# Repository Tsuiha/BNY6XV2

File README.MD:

# BNY6X V2

「BNY6X V2」は2025年に製作した60%キーボードです。  
多親指キー＋矢印キー配列、MXとロープロに両対応、GH60互換ケース対応、の特徴があります。

---

## BNY6X V2 PCB

- **キー配列**
60%レイアウト  
親指キー、矢印キーを備えた最下行  

[Keyboard Layout Editor](https://www.keyboard-layout-editor.com/)

- **対応マウント方式**
GH60互換設計で、6か所のネジ穴が設けられています。  
加えて外周に5か所の切り欠きが設けられており、独自のプレートマウントにも対応します。

- **対応スイッチ**
「Cherry MX 」または「KS-33B GateronLowProfile 3.0」に互換性のあるスイッチが使用できます。  
キースイッチはMX用ホットスワップソケットにてPCBに接続します。
ロープロ対応及び低背化のため基板は1.2mm を使用します。

- **サイドスイッチ**
背面type-C横には3方向（左、右、押し込み）のレバースイッチが取り付け可能です。  
既製品のGH60互換ケースに使用する際は、干渉するためレバースイッチは実装しない必要があります。

- **対応スタビライザー**
プレートマウントのスタビライザーにのみ対応します。  
またMXスイッチの場合スタビライザー下が開いているため、ケース取り付け前に予めスタビライザー部のキーキャップは取り付けておく必要があります。

- **Firmware**
QMK Fimware, [BNY6X V2 codes](https://github.com/Tsuiha/vial-qmk/tree/vial/keyboards/0_tsuiha/bny6x_v2)

---

## BNY6X V2 typeT

1ピースでCNC加工を想定したGH60互換トレイケースです。

- **マウント箇所**
左右4か所のみネジ受けを設けており、中央2か所は省いています。  
ねじ止めで位置を固定し、ボトムフォームで基板を保持する機構です。

- **フロントベゼル幅**
フロントトップのベゼルをカットし幅を抑えています。  
指付け根でのキー入力時に干渉しにくいです。

- **低背設計**
高さを抑えているため、手前部に背の高い実装部品や下付きソケットの基板の場合ケースに干渉する恐れがあります。

- **チルト角**
6度固定です。

- **type-C開口**
上方向に余裕があるため、手前部に基板の干渉がある場合、スタンドオフにスペーサを噛ませることで干渉を回避できます。  
また横方向のtype-C位置はGH60、Wootingの両方に対応します。

---

## BNY6X V2 typeL

BNY6X V2用に設計しました。  
2ピースでCNC加工を想定したKS33-Bスイッチ用のBNY6X V2 PCBケースです。

- **対応スタビライザー**
Gateron KS-57　ロープロファイルスイッチ用スタビライザーに対応しています。

- **マウント方式**
BNY6X V2 PCBの切り欠き部を介しトップケースとボトムケースとをねじ止めしマウントします。

- **レバースイッチ**
背面はレバースイッチの実装に対応しています。

- **コンパクト設計**
高さとベゼル幅を抑えたコンパクトな外形です。

- **チルト角**
6度固定です。

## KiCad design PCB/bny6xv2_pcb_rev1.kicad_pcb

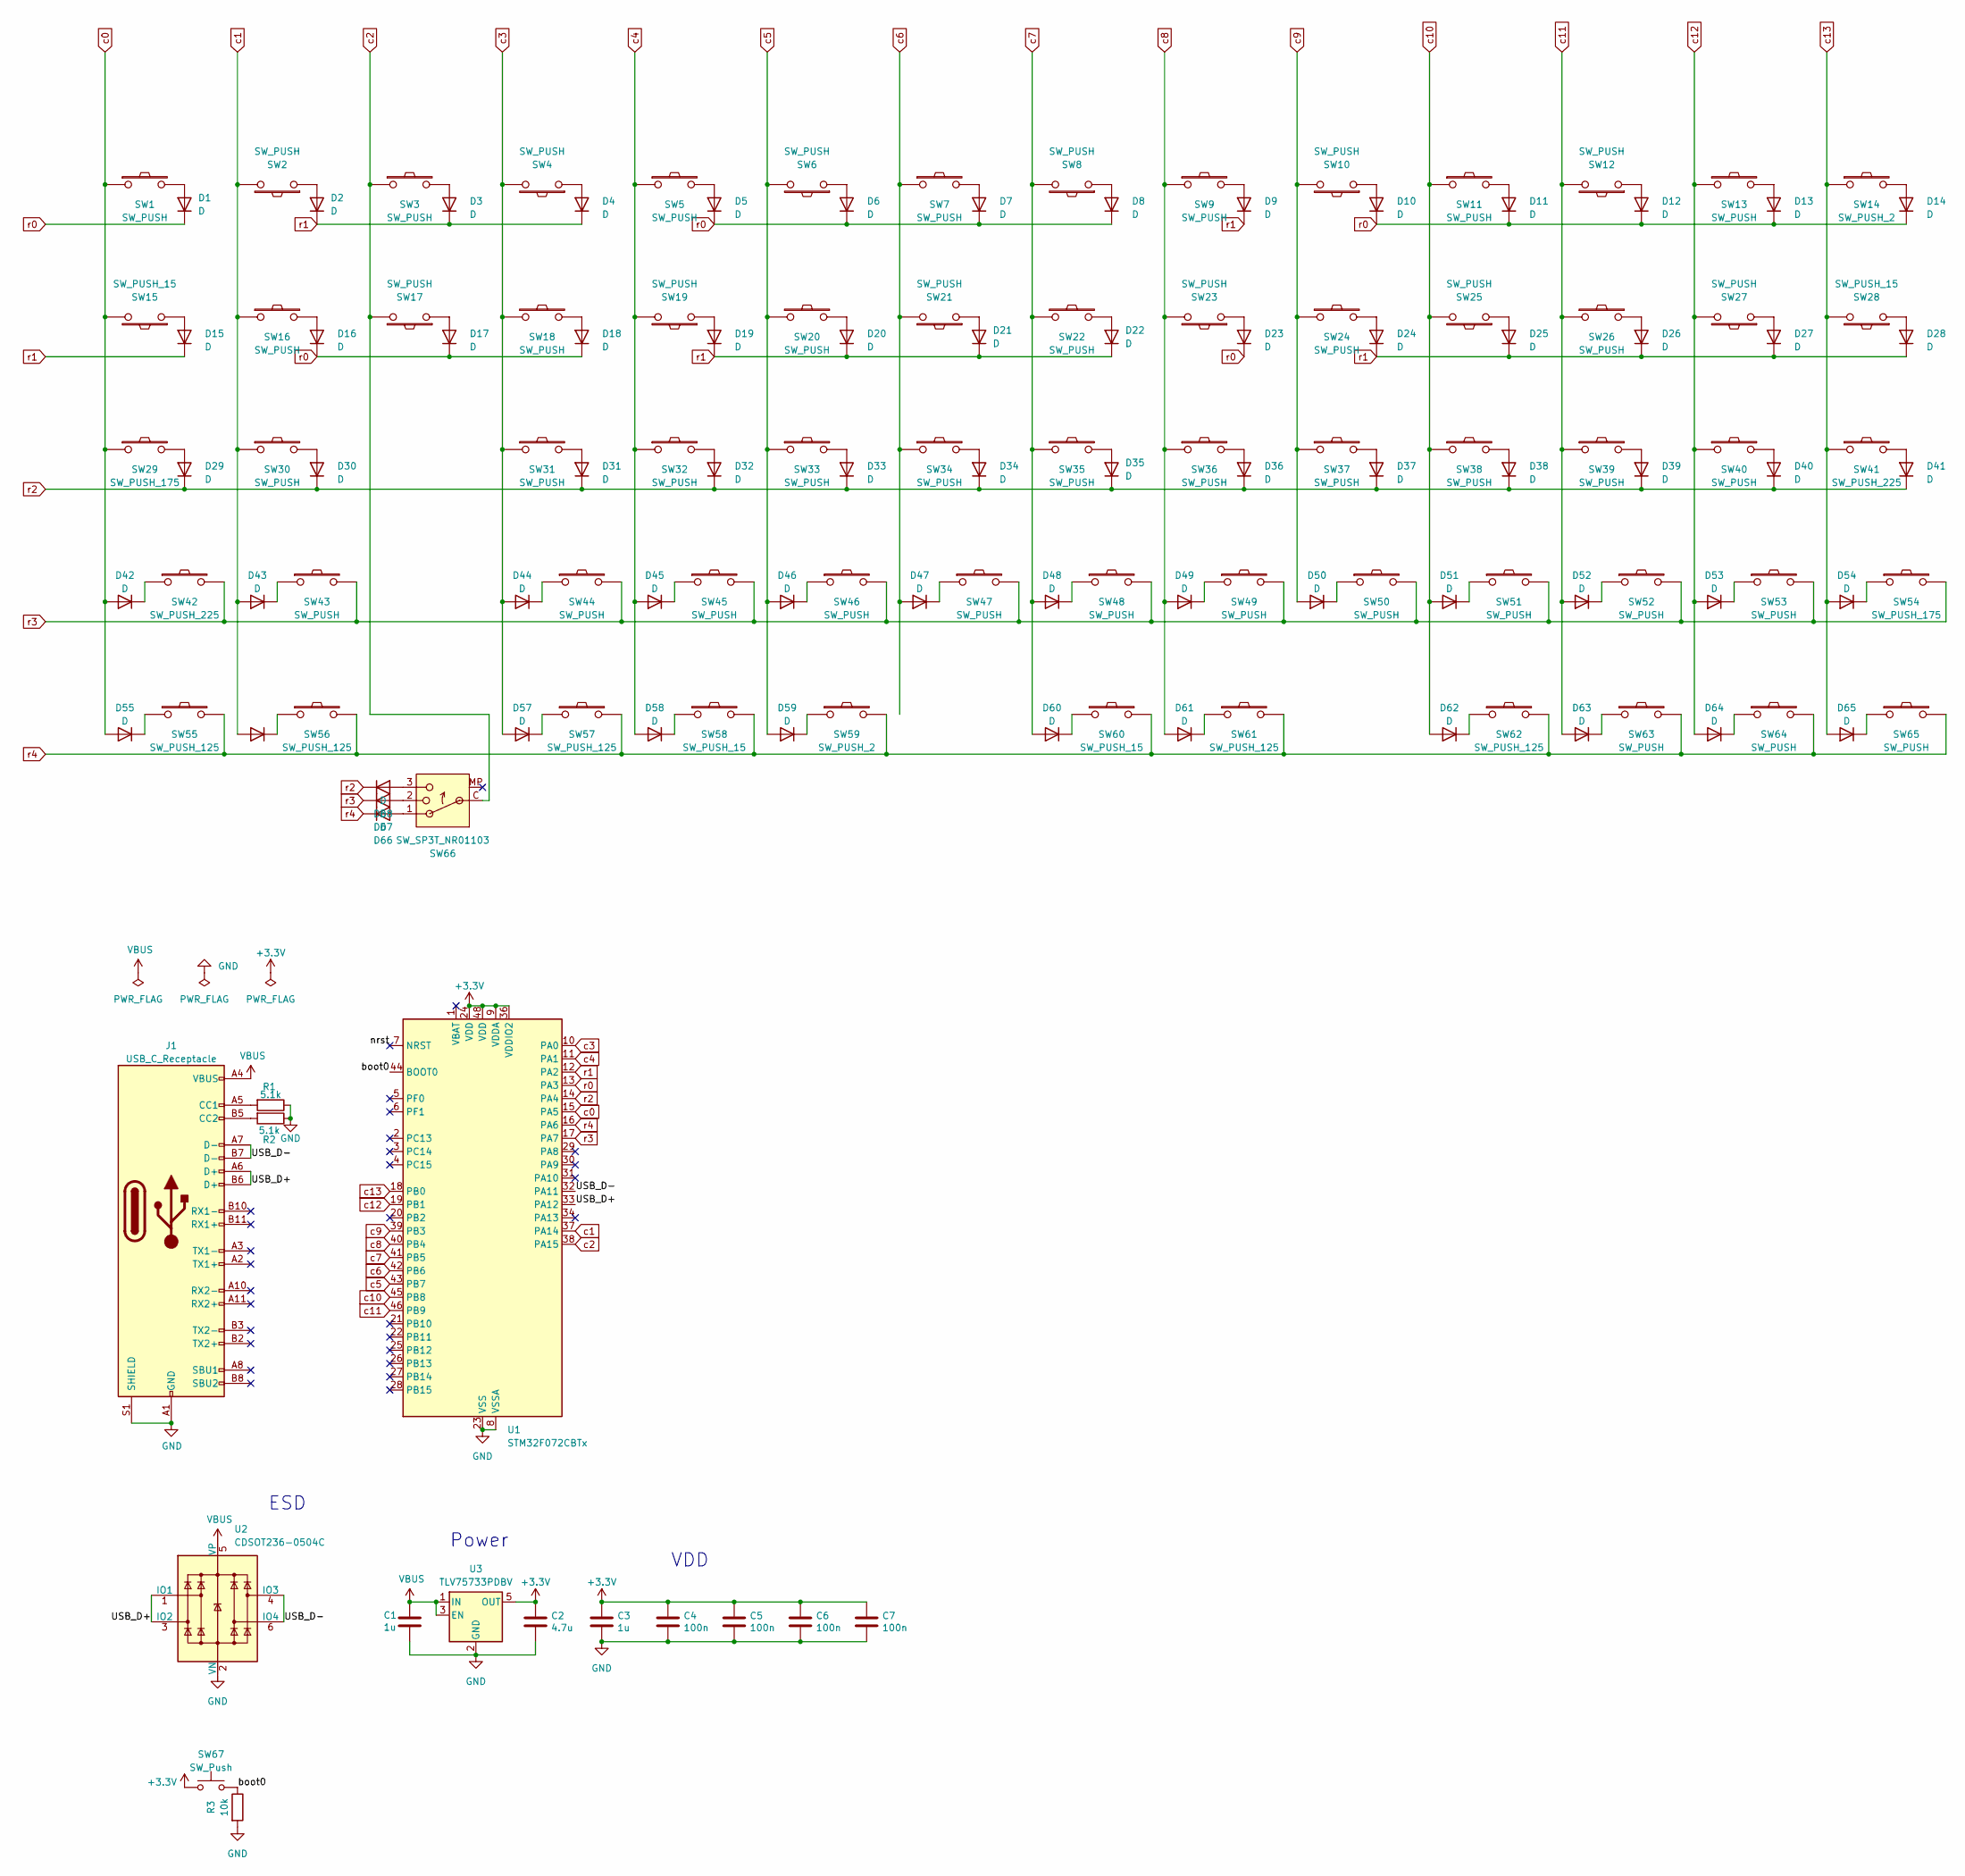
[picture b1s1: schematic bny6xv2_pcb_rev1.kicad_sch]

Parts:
C1, C3: 1u; C_0603_1608Metric
C2: 4.7u; C_0603_1608Metric
C4, C5, C6, C7: 100n; C_0603_1608Metric
D1, D2, D3, D4, D5, D6, D7, D8, D9, D10, D11, D12, D13, D14, D15, D16, D17, D18, D19, D20, D21, D22, D23, D24, D25, D26, D27, D28, D29, D30, D31, D32, D33, D34, D35, D36, D37, D38, D39, D40, D41, D42, D43, D44, D45, D46, D47, D48, D49, D50, D51, D52, D53, D54, D55, D56, D57, D58, D59, D60, D61, D62, D63, D64, D65, D66, D67, D68: D; Diode_SMD_noname
J1: USB_C_Receptacle; USB_C_Receptacle_HRO_TYPE-C-31-M-12_My
R1, R2: 5.1k; C_0603_1608Metric
R3: 10k; C_0603_1608Metric
SW1, SW2, SW3, SW4, SW5, SW6, SW7, SW8, SW9, SW10, SW11, SW12, SW13, SW16, SW17, SW18, SW19, SW20, SW21, SW22, SW23, SW24, SW25, SW26, SW27, SW30, SW31, SW32, SW33, SW34, SW35, SW36, SW37, SW38, SW39, SW40, SW43, SW44, SW45, SW46, SW47, SW48, SW49, SW50, SW51, SW52, SW53, SW63, SW64, SW65: SW_PUSH; GLPV3_1U
SW14, SW59: SW_PUSH_2; GLPV3_2u_r
SW15, SW28: SW_PUSH_15; GLPV3_1.5U
SW29: SW_PUSH_175; GLPV3_1.75U
SW41: SW_PUSH_225; GLPV3_2.25u
SW42: SW_PUSH_225; GLPV3_2.25u_r
SW54: SW_PUSH_175; MX_GLPV3_1.75U
SW55, SW56, SW57, SW62: SW_PUSH_125; GLPV3_1.25U
SW58: SW_PUSH_15; GLPV3_1U
SW60: SW_PUSH_15; GLPV3_2u_r
SW61: SW_PUSH_125; GLPV3_1U
SW66: SW_SP3T_NR01103; TMHU27
SW67: SW_Push; SW_SPST_SKQG_WithStem
U1: STM32F072CBTx; LQFP-48_7x7mm_P0.5mm
U2: CDSOT236-0504C; sot-23-6-USBESD
U3: TLV75733PDBV; SOT-23-5

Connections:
+3.3V: C2.1, C3.1, C4.1, C5.1, C6.1, C7.1, SW67.1, U1.9 (VDDA), U1.24 (VDD), U1.36 (VDDIO2), U1.48 (VDD), U3.5 (OUT)
/USB_D+: J1.A6 (D+), J1.B6 (D+), U1.33 (PA12), U2.1 (IO1), U2.3 (IO2)
/USB_D-: J1.A7 (D-), J1.B7 (D-), U1.32 (PA11), U2.4 (IO3), U2.6 (IO4)
/boot0: R3.1, SW67.2, U1.44 (BOOT0)
/nrst: U1.7 (NRST)
GND: C1.2, C2.2, C3.2, C4.2, C5.2, C6.2, C7.2, J1.A1 (GND), J1.A12 (GND), J1.B1 (GND), J1.B12 (GND), J1.S1 (SHIELD), R1.1, R2.1, R3.2, U1.8 (VSSA), U1.23 (VSS), U1.35 (VSS), U1.47 (VSS), U2.2 (VN), U3.2 (GND)
unnamed: D1.2 (A), SW1.2
unnamed: D2.2 (A), SW2.1
unnamed: D3.2 (A), SW3.2
unnamed: D4.2 (A), SW4.1
unnamed: D5.2 (A), SW5.2
unnamed: D6.2 (A), SW6.1
unnamed: D7.2 (A), SW7.2
unnamed: D8.2 (A), SW8.1
unnamed: D9.2 (A), SW9.2
unnamed: D10.2 (A), SW10.1
unnamed: D11.2 (A), SW11.2
unnamed: D12.2 (A), SW12.1
unnamed: D13.2 (A), SW13.2
unnamed: D14.2 (A), SW14.2
unnamed: D15.2 (A), SW15.1
unnamed: D16.2 (A), SW16.2
unnamed: D17.2 (A), SW17.1
unnamed: D18.2 (A), SW18.2
unnamed: D19.2 (A), SW19.1
unnamed: D20.2 (A), SW20.2
unnamed: D21.2 (A), SW21.1
unnamed: D22.2 (A), SW22.2
unnamed: D23.2 (A), SW23.1
unnamed: D24.2 (A), SW24.2
unnamed: D25.2 (A), SW25.1
unnamed: D26.2 (A), SW26.2
unnamed: D27.2 (A), SW27.1
unnamed: D28.2 (A), SW28.1
unnamed: D29.2 (A), SW29.2
unnamed: D30.2 (A), SW30.2
unnamed: D31.2 (A), SW31.2
unnamed: D32.2 (A), SW32.2
unnamed: D33.2 (A), SW33.2
unnamed: D34.2 (A), SW34.2
unnamed: D35.2 (A), SW35.2
unnamed: D36.2 (A), SW36.2
unnamed: D37.2 (A), SW37.2
unnamed: D38.2 (A), SW38.2
unnamed: D39.2 (A), SW39.2
unnamed: D40.2 (A), SW40.2
unnamed: D41.2 (A), SW41.2
unnamed: D42.1 (K), SW42.1
unnamed: D43.1 (K), SW43.1
unnamed: D44.1 (K), SW44.1
unnamed: D45.1 (K), SW45.1
unnamed: D46.1 (K), SW46.1
unnamed: D47.1 (K), SW47.1
unnamed: D48.1 (K), SW48.1
unnamed: D49.1 (K), SW49.1
unnamed: D50.1 (K), SW50.1
unnamed: D51.1 (K), SW51.1
unnamed: D52.1 (K), SW52.1
unnamed: D53.1 (K), SW53.1
unnamed: D54.1 (K), SW54.1
unnamed: D55.1 (K), SW55.1
unnamed: D56.1 (K), SW56.1
unnamed: D57.1 (K), SW57.1
unnamed: D58.1 (K), SW58.1
unnamed: D59.1 (K), SW59.1
unnamed: D60.1 (K), SW60.1
unnamed: D61.1 (K), SW61.1
unnamed: D62.1 (K), SW62.1
unnamed: D63.1 (K), SW63.1
unnamed: D64.1 (K), SW64.1
unnamed: D65.1 (K), SW65.1
unnamed: D66.2 (A), SW66.1
unnamed: D67.2 (A), SW66.2
unnamed: D68.2 (A), SW66.3
unnamed: J1.A5 (CC1), R1.2
unnamed: J1.B5 (CC2), R2.2
VBUS: C1.1, J1.A4 (VBUS), J1.A9 (VBUS), J1.B4 (VBUS), J1.B9 (VBUS), U2.5 (VP), U3.1 (IN), U3.3 (EN)
c0: D42.2 (A), D55.2 (A), SW1.1, SW15.2, SW29.1, U1.15 (PA5)
c1: D43.2 (A), D56.2 (A), SW2.2, SW16.1, SW30.1, U1.37 (PA14)
c2: SW3.1, SW17.2, SW66.C (Common), U1.38 (PA15)
c3: D44.2 (A), D57.2 (A), SW4.2, SW18.1, SW31.1, U1.10 (PA0)
c4: D45.2 (A), D58.2 (A), SW5.1, SW19.2, SW32.1, U1.11 (PA1)
c5: D46.2 (A), D59.2 (A), SW6.2, SW20.1, SW33.1, U1.43 (PB7)
c6: D47.2 (A), SW7.1, SW21.2, SW34.1, U1.42 (PB6)
c7: D48.2 (A), D60.2 (A), SW8.2, SW22.1, SW35.1, U1.41 (PB5)
c8: D49.2 (A), D61.2 (A), SW9.1, SW23.2, SW36.1, U1.40 (PB4)
c9: D50.2 (A), SW10.2, SW24.1, SW37.1, U1.39 (PB3)
c10: D51.2 (A), D62.2 (A), SW11.1, SW25.2, SW38.1, U1.45 (PB8)
c11: D52.2 (A), D63.2 (A), SW12.2, SW26.1, SW39.1, U1.46 (PB9)
c12: D53.2 (A), D64.2 (A), SW13.1, SW27.2, SW40.1, U1.19 (PB1)
c13: D54.2 (A), D65.2 (A), SW14.1, SW28.2, SW41.1, U1.18 (PB0)
r0: D1.1 (K), D5.1 (K), D6.1 (K), D7.1 (K), D8.1 (K), D10.1 (K), D11.1 (K), D12.1 (K), D13.1 (K), D14.1 (K), D16.1 (K), D17.1 (K), D18.1 (K), D23.1 (K), U1.13 (PA3)
r1: D2.1 (K), D3.1 (K), D4.1 (K), D9.1 (K), D15.1 (K), D19.1 (K), D20.1 (K), D21.1 (K), D22.1 (K), D24.1 (K), D25.1 (K), D26.1 (K), D27.1 (K), D28.1 (K), U1.12 (PA2)
r2: D29.1 (K), D30.1 (K), D31.1 (K), D32.1 (K), D33.1 (K), D34.1 (K), D35.1 (K), D36.1 (K), D37.1 (K), D38.1 (K), D39.1 (K), D40.1 (K), D41.1 (K), D68.1 (K), U1.14 (PA4)
r3: D67.1 (K), SW42.2, SW43.2, SW44.2, SW45.2, SW46.2, SW47.2, SW48.2, SW49.2, SW50.2, SW51.2, SW52.2, SW53.2, SW54.2, U1.17 (PA7)
r4: D66.1 (K), SW55.2, SW56.2, SW57.2, SW58.2, SW59.2, SW60.2, SW61.2, SW62.2, SW63.2, SW64.2, SW65.2, U1.16 (PA6)

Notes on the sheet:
Power
ESD
VDD

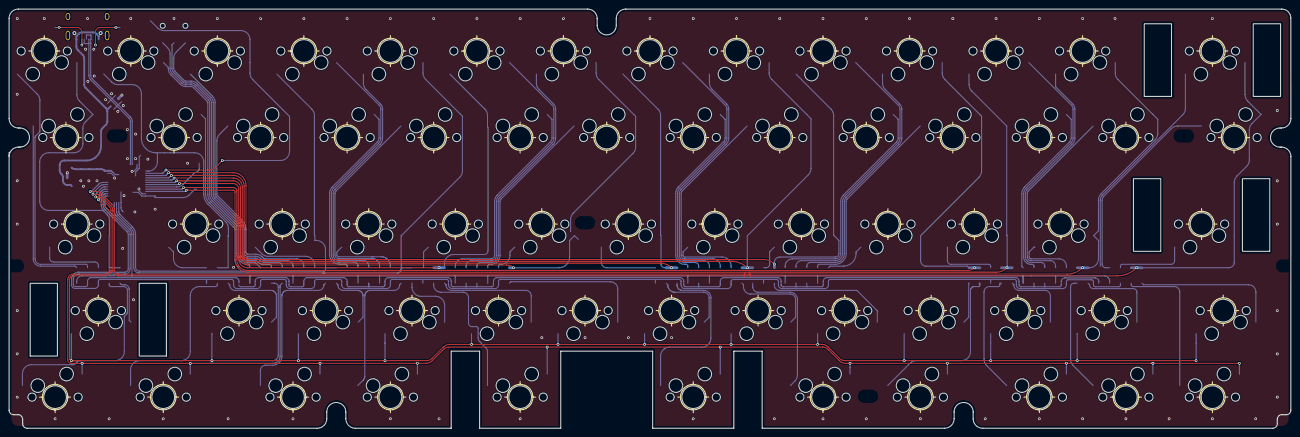
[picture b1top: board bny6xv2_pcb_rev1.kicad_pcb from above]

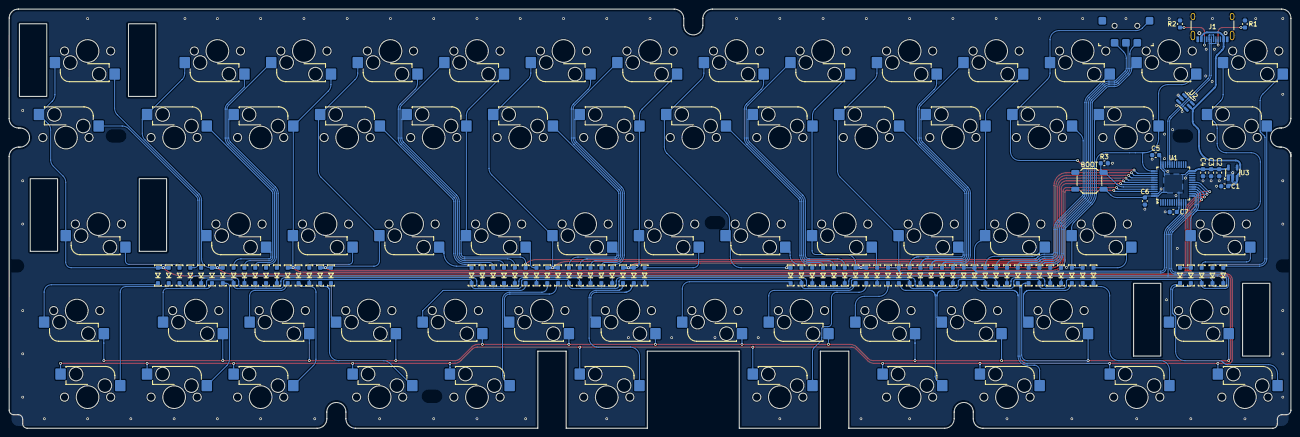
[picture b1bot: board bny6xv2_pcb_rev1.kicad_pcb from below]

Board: 2 copper layers, 282.1 x 92.2 mm, 149 parts (16 on the bottom side), 95 nets.

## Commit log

2025-11-12 Update README with BNY6X V2 details
